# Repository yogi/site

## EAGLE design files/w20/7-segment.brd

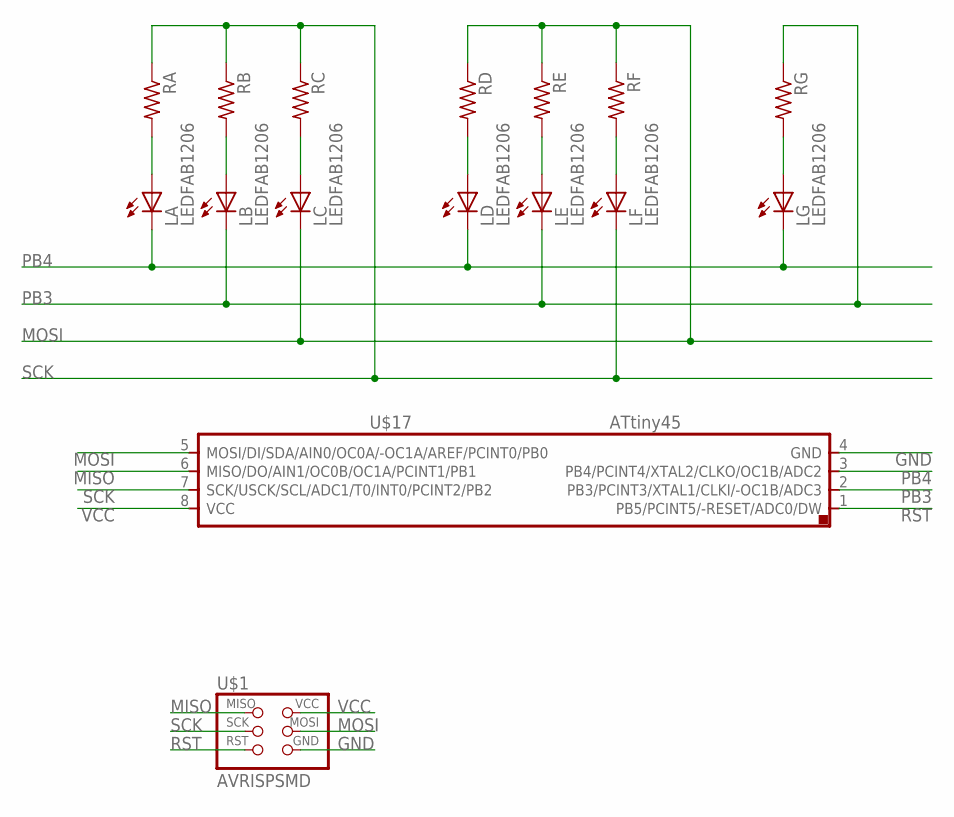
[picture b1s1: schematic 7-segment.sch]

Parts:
LA: LEDFAB1206; LED1206FAB
LB: LEDFAB1206; LED1206FAB
LC: LEDFAB1206; LED1206FAB
LD: LEDFAB1206; LED1206FAB
LE: LEDFAB1206; LED1206FAB
LF: LEDFAB1206; LED1206FAB
LG: LEDFAB1206; LED1206FAB
RA: RES-US1206FAB; R1206FAB
RB: RES-US1206FAB; R1206FAB
RC: RES-US1206FAB; R1206FAB
RD: RES-US1206FAB; R1206FAB
RE: RES-US1206FAB; R1206FAB
RF: RES-US1206FAB; R1206FAB
RG: RES-US1206FAB; R1206FAB
U$1: AVRISPSMD; 2X03SMD
U$17: ATTINY45SI; SOIC8

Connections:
GND: U$1.6 (GND), U$17.4 (GND)
MISO: U$1.1 (MISO), U$17.6 (MISO/DO/AIN1/OC0B/OC1A/PCINT1/PB1)
MOSI: LC.2 (C), RD.1, RE.1, RF.1, U$1.4 (MOSI), U$17.5 (MOSI/DI/SDA/AIN0/OC0A/-OC1A/AREF/PCINT0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)
unnamed: LA.1 (A), RA.2
unnamed: LB.1 (A), RB.2
unnamed: LC.1 (A), RC.2
unnamed: LD.1 (A), RD.2
unnamed: LE.1 (A), RE.2
unnamed: LF.1 (A), RF.2
unnamed: LG.1 (A), RG.2
PB3: LB.2 (C), LE.2 (C), RG.1, U$17.2 (PB3/PCINT3/XTAL1/CLKI/-OC1B/ADC3)
PB4: LA.2 (C), LD.2 (C), LG.2 (C), U$17.3 (PB4/PCINT4/XTAL2/CLKO/OC1B/ADC2)
RST: U$1.5 (RST), U$17.1 (PB5/PCINT5/-RESET/ADC0/DW)
SCK: LF.2 (C), RA.1, RB.1, RC.1, U$1.3 (SCK), U$17.7 (SCK/USCK/SCL/ADC1/T0/INT0/PCINT2/PB2)
VCC: U$1.2 (VCC), U$17.8 (VCC)

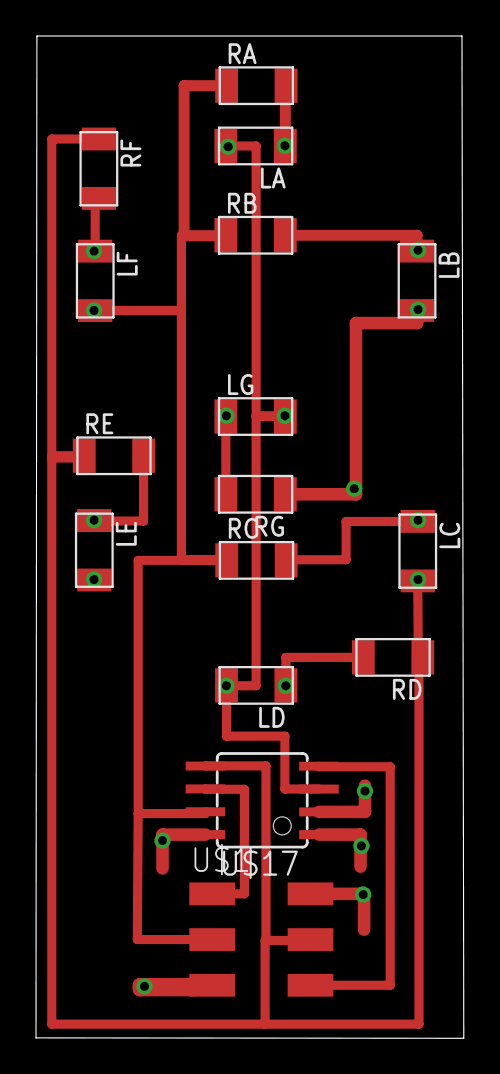
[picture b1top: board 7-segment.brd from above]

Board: 2 copper layers, 23.8 x 55.7 mm, 16 parts (0 on the bottom side), 15 nets.

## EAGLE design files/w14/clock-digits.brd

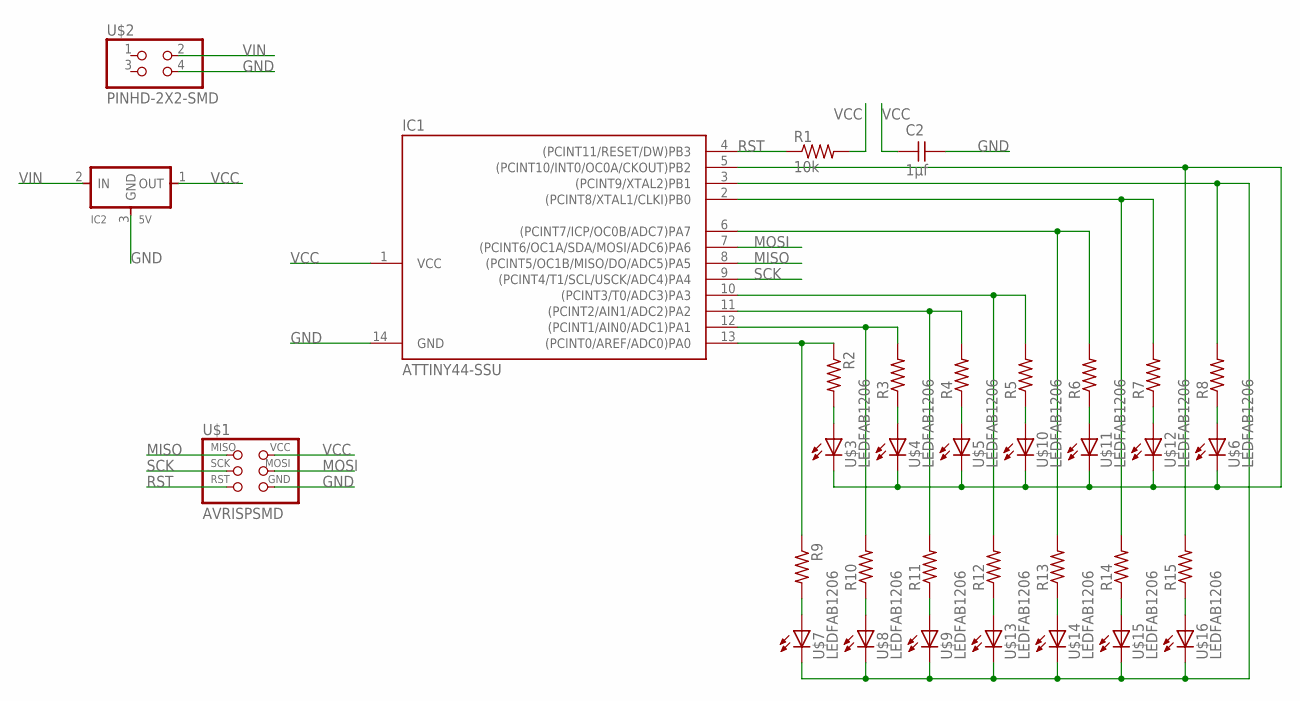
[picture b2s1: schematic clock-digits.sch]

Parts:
C2: 1µf; C1206FAB
IC1: ATTINY44-SSU; SOIC14
IC2: 5V; SOT23
R1: 10k; R1206FAB
R2, R3, R4, R5, R6, R7, R8, R9, R10, R11, R12, R13, R14, R15: RES-US1206FAB; R1206FAB
U$1: AVRISPSMD; 2X03SMD
U$2: PINHD-2X2-SMD; 2X02SMD
U$3, U$4, U$5, U$6, U$7, U$8, U$9, U$10, U$11, U$12, U$13, U$14, U$15, U$16: LEDFAB1206; LED1206FAB

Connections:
GND: C2.2, IC1.14 (GND), IC2.3 (GND), U$1.6 (GND), U$2.4
MISO: IC1.8 ((PCINT5/OC1B/MISO/DO/ADC5)PA5), U$1.1 (MISO)
MOSI: IC1.7 ((PCINT6/OC1A/SDA/MOSI/ADC6)PA6), U$1.4 (MOSI)
unnamed: IC1.13 ((PCINT0/AREF/ADC0)PA0), R2.1, R9.1
unnamed: R2.2, U$3.1 (A)
unnamed: IC1.12 ((PCINT1/AIN0/ADC1)PA1), R3.2, R10.2
unnamed: R3.1, U$4.1 (A)
unnamed: IC1.11 ((PCINT2/AIN1/ADC2)PA2), R4.2, R11.2
unnamed: R4.1, U$5.1 (A)
unnamed: IC1.10 ((PCINT3/T0/ADC3)PA3), R5.2, R12.2
unnamed: R5.1, U$10.1 (A)
unnamed: IC1.6 ((PCINT7/ICP/OC0B/ADC7)PA7), R6.2, R13.2
unnamed: R6.1, U$11.1 (A)
unnamed: IC1.2 ((PCINT8/XTAL1/CLKI)PB0), R7.2, R14.2
unnamed: R7.1, U$12.1 (A)
unnamed: R8.1, U$6.1 (A)
unnamed: IC1.5 ((PCINT10/INT0/OC0A/CKOUT)PB2), R15.2, U$3.2 (C), U$4.2 (C), U$5.2 (C), U$6.2 (C), U$10.2 (C), U$11.2 (C), U$12.2 (C)
unnamed: R9.2, U$7.1 (A)
unnamed: R15.1, U$16.1 (A)
unnamed: R10.1, U$8.1 (A)
unnamed: R11.1, U$9.1 (A)
unnamed: R12.1, U$13.1 (A)
unnamed: R13.1, U$14.1 (A)
unnamed: R14.1, U$15.1 (A)
unnamed: IC1.3 ((PCINT9/XTAL2)PB1), R8.2, U$7.2 (C), U$8.2 (C), U$9.2 (C), U$13.2 (C), U$14.2 (C), U$15.2 (C), U$16.2 (C)
RST: IC1.4 ((PCINT11/RESET/DW)PB3), R1.1, U$1.5 (RST)
SCK: IC1.9 ((PCINT4/T1/SCL/USCK/ADC4)PA4), U$1.3 (SCK)
VCC: C2.1, IC1.1 (VCC), IC2.1 (OUT), R1.2, U$1.2 (VCC)
VIN: IC2.2 (IN), U$2.2

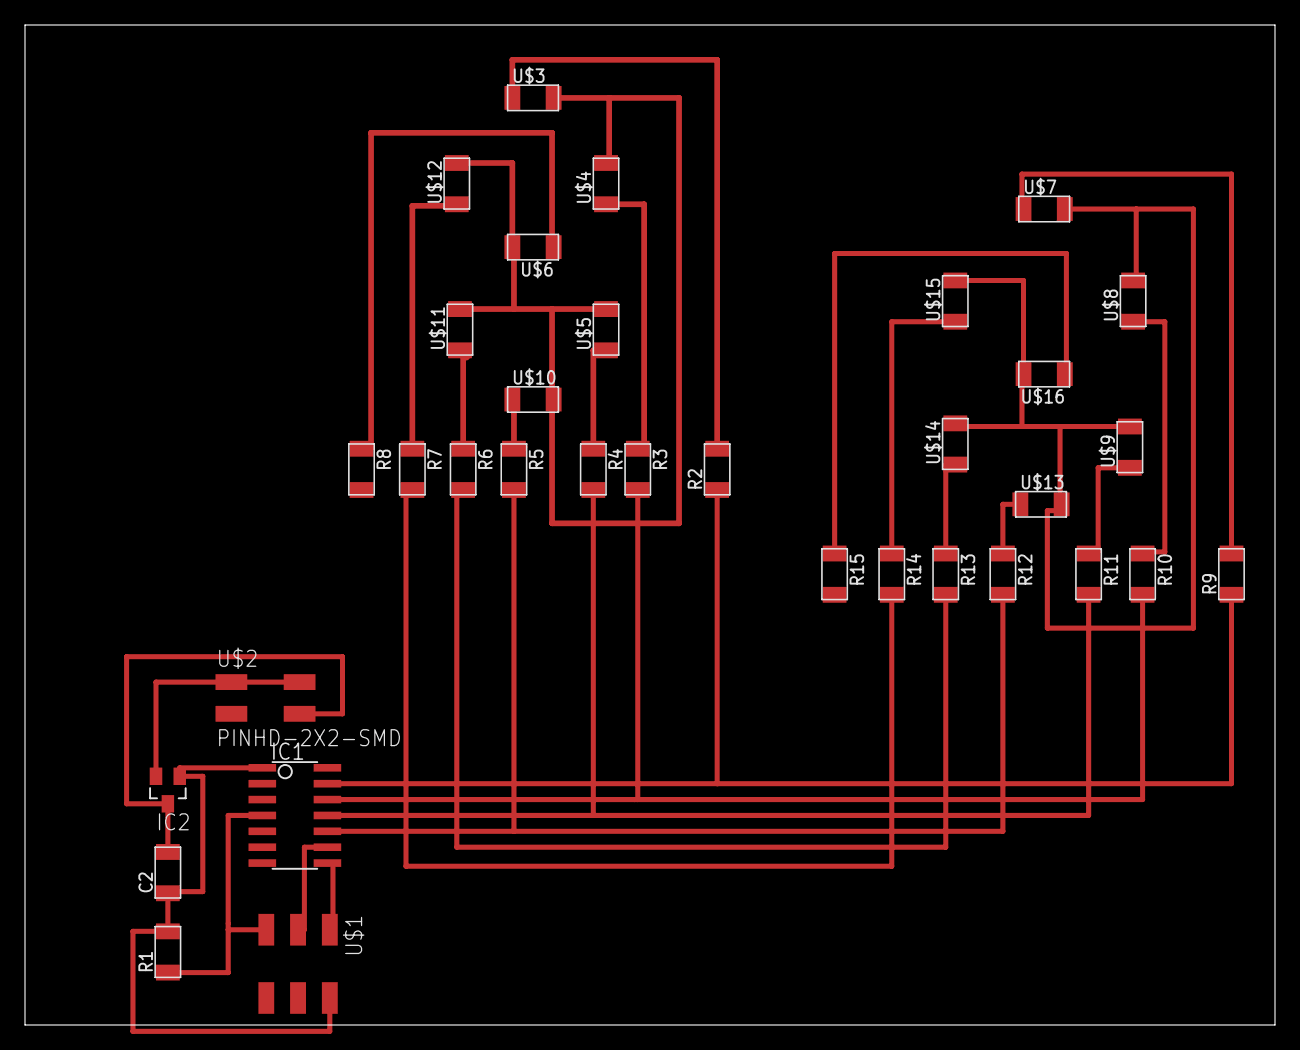
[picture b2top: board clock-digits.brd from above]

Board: 2 copper layers, 100.0 x 80.0 mm, 34 parts (0 on the bottom side), 29 nets.

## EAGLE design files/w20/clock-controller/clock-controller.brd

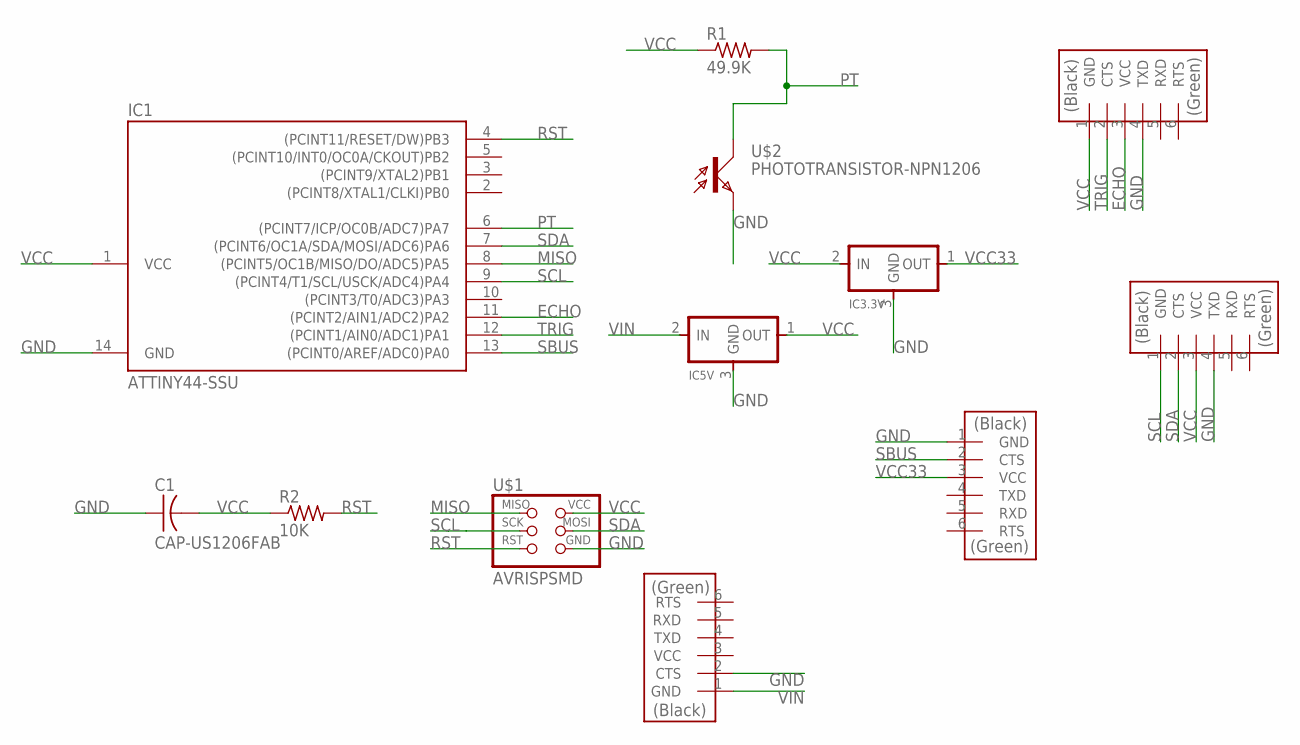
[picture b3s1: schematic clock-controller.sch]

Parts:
C1: CAP-US1206FAB; C1206FAB
DIGITS: FTDI-SMD-HEADER; 1X06SMD
IC1: ATTINY44-SSU; SOIC14
IC3.3V, IC5V: REGULATORSOT23; SOT23
R1: 49.9K; R1206FAB
R2: 10K; R1206FAB
RTC: FTDI-SMD-HEADER; 1X06SMD
U$1: AVRISPSMD; 2X03SMD
U$2: PHOTOTRANSISTOR-NPN1206; OP1206
ULTRA: FTDI-SMD-HEADER; 1X06SMD
USB: FTDI-SMD-HEADER; 1X06SMD

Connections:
ECHO: IC1.11 ((PCINT2/AIN1/ADC2)PA2), ULTRA.3 (VCC)
GND: C1.1, DIGITS.1 (GND), IC1.14 (GND), IC3.3V.3 (GND), IC5V.3 (GND), RTC.4 (TXD), U$1.6 (GND), U$2.EMITTER (E), ULTRA.4 (TXD), USB.2 (CTS)
MISO: IC1.8 ((PCINT5/OC1B/MISO/DO/ADC5)PA5), U$1.1 (MISO)
PT: IC1.6 ((PCINT7/ICP/OC0B/ADC7)PA7), R1.2, U$2.COLLECTOR (C)
RST: IC1.4 ((PCINT11/RESET/DW)PB3), R2.2, U$1.5 (RST)
SBUS: DIGITS.2 (CTS), IC1.13 ((PCINT0/AREF/ADC0)PA0)
SCL: IC1.9 ((PCINT4/T1/SCL/USCK/ADC4)PA4), RTC.1 (GND), U$1.3 (SCK)
SDA: IC1.7 ((PCINT6/OC1A/SDA/MOSI/ADC6)PA6), RTC.2 (CTS), U$1.4 (MOSI)
TRIG: IC1.12 ((PCINT1/AIN0/ADC1)PA1), ULTRA.2 (CTS)
VCC: C1.2, IC1.1 (VCC), IC3.3V.2 (IN), IC5V.1 (OUT), R1.1, R2.1, RTC.3 (VCC), U$1.2 (VCC), ULTRA.1 (GND)
VCC33: DIGITS.3 (VCC), IC3.3V.1 (OUT)
VIN: IC5V.2 (IN), USB.1 (GND)

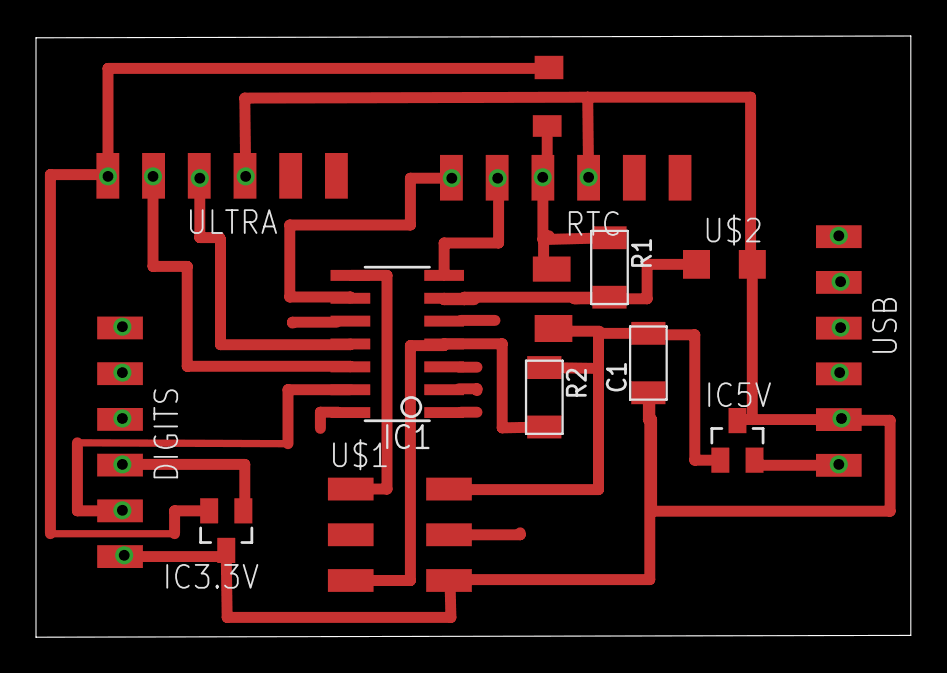
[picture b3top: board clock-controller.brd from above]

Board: 2 copper layers, 48.6 x 33.4 mm, 12 parts (0 on the bottom side), 12 nets.

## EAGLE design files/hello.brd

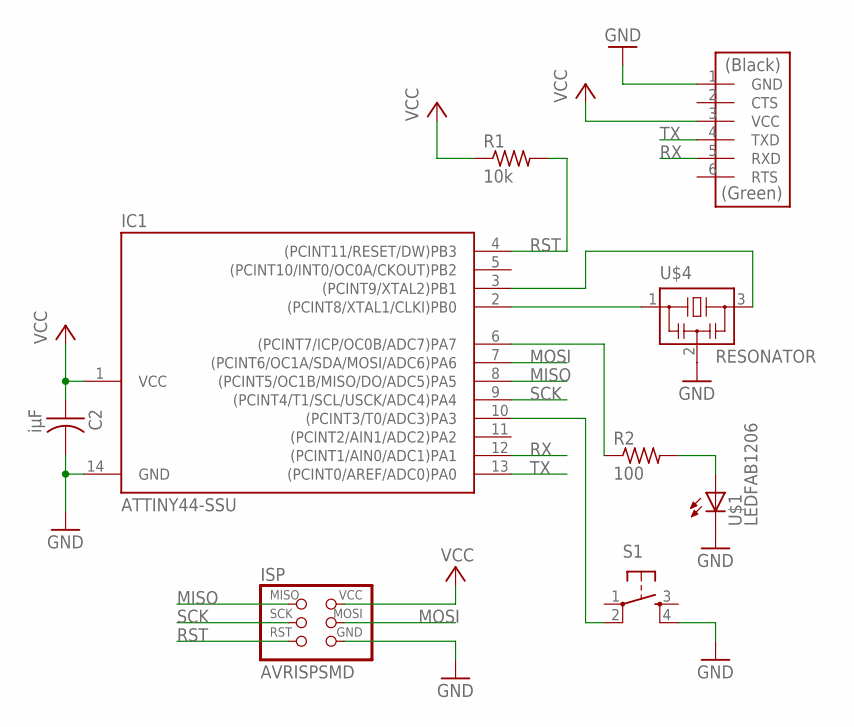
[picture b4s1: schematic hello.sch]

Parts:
C2: iµF; C1206
IC1: ATTINY44-SSU; SOIC14
ISP: AVRISPSMD; 2X03SMD
R1: 10k; R1206
R2: 100; R1206
S1: 6MM_SWITCH6MM_SWITCH; 6MM_SWITCH
U$1: LEDFAB1206; LED1206FAB
U$2: FTDI-SMD-HEADER; 1X06SMD
U$4: RESONATOR; EFOBM

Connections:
GND: C2.2, IC1.14 (GND), ISP.6 (GND), S1.4 (S1), U$1.2 (C), U$2.1 (GND), U$4.2
MISO: IC1.8 ((PCINT5/OC1B/MISO/DO/ADC5)PA5), ISP.1 (MISO)
MOSI: IC1.7 ((PCINT6/OC1A/SDA/MOSI/ADC6)PA6), ISP.4 (MOSI)
unnamed: IC1.2 ((PCINT8/XTAL1/CLKI)PB0), U$4.1
unnamed: IC1.3 ((PCINT9/XTAL2)PB1), U$4.3
unnamed: IC1.6 ((PCINT7/ICP/OC0B/ADC7)PA7), R2.1
unnamed: R2.2, U$1.1 (A)
unnamed: IC1.10 ((PCINT3/T0/ADC3)PA3), S1.2 (P1)
RST: IC1.4 ((PCINT11/RESET/DW)PB3), ISP.5 (RST), R1.2
RX: IC1.12 ((PCINT1/AIN0/ADC1)PA1), U$2.5 (RXD)
SCK: IC1.9 ((PCINT4/T1/SCL/USCK/ADC4)PA4), ISP.3 (SCK)
TX: IC1.13 ((PCINT0/AREF/ADC0)PA0), U$2.4 (TXD)
VCC: C2.1, IC1.1 (VCC), ISP.2 (VCC), R1.1, U$2.3 (VCC)

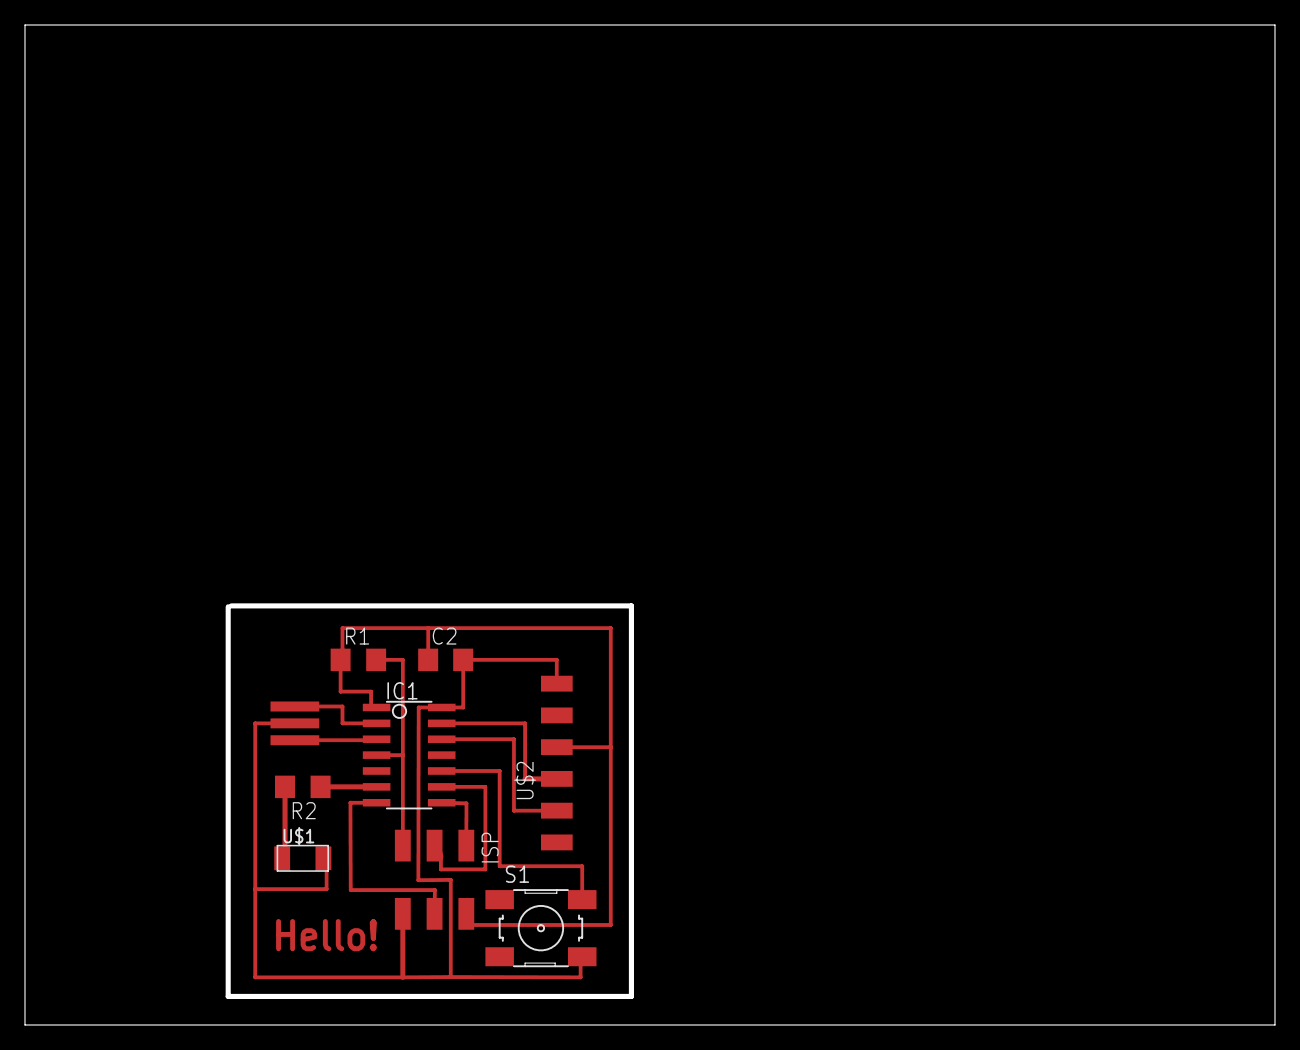
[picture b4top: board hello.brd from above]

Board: 2 copper layers, 100.0 x 80.0 mm, 9 parts (0 on the bottom side), 13 nets.

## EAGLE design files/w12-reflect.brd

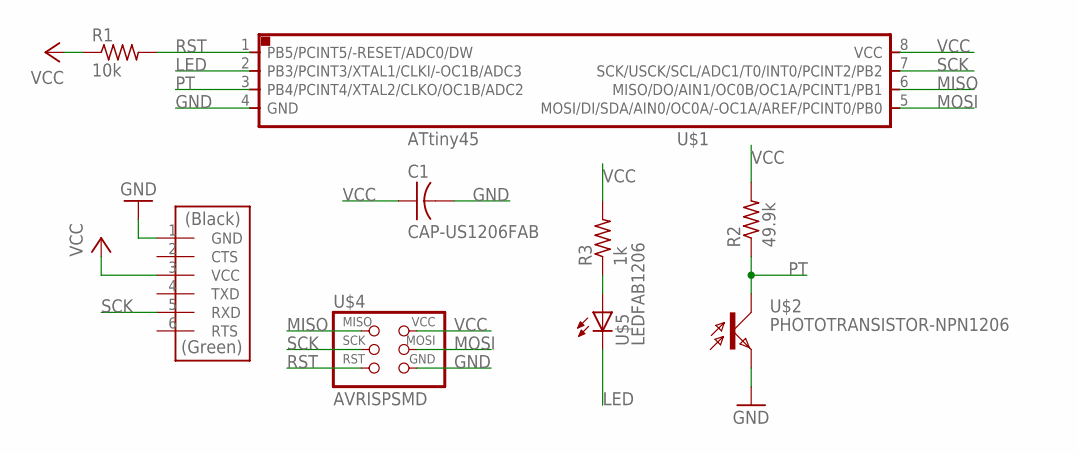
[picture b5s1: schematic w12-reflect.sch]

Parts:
C1: CAP-US1206FAB; C1206FAB
R1: 10k; R1206FAB
R2: 49.9k; R1206FAB
R3: 1k; R1206FAB
U$1: ATTINY45SI; SOIC8
U$2: PHOTOTRANSISTOR-NPN1206; OP1206
U$3: FTDI-SMD-HEADER; 1X06SMD
U$4: AVRISPSMD; 2X03SMD
U$5: LEDFAB1206; LED1206FAB

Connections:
GND: C1.2, U$1.4 (GND), U$2.EMITTER (E), U$3.1 (GND), U$4.6 (GND)
LED: U$1.2 (PB3/PCINT3/XTAL1/CLKI/-OC1B/ADC3), U$5.2 (C)
MISO: U$1.6 (MISO/DO/AIN1/OC0B/OC1A/PCINT1/PB1), U$4.1 (MISO)
MOSI: U$1.5 (MOSI/DI/SDA/AIN0/OC0A/-OC1A/AREF/PCINT0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), U$4.4 (MOSI)
unnamed: R3.1, U$5.1 (A)
PT: R2.1, U$1.3 (PB4/PCINT4/XTAL2/CLKO/OC1B/ADC2), U$2.COLLECTOR (C)
RST: R1.2, U$1.1 (PB5/PCINT5/-RESET/ADC0/DW), U$4.5 (RST)
SCK: U$1.7 (SCK/USCK/SCL/ADC1/T0/INT0/PCINT2/PB2), U$3.5 (RXD), U$4.3 (SCK)
VCC: C1.1, R1.1, R2.2, R3.2, U$1.8 (VCC), U$3.3 (VCC), U$4.2 (VCC)

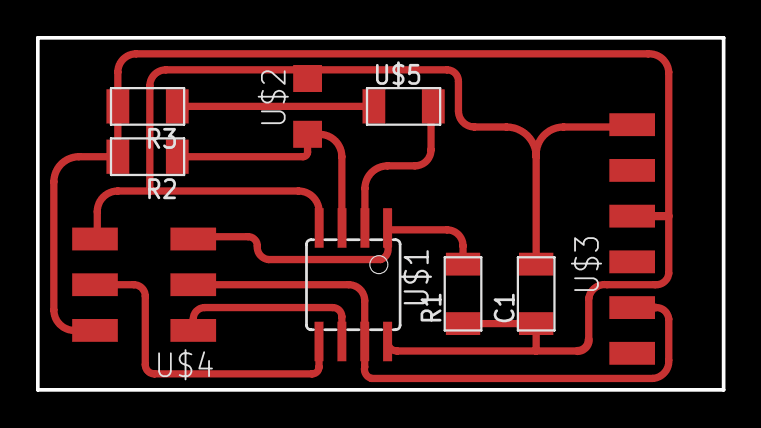
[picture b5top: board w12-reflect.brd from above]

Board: 2 copper layers, 38.1 x 19.6 mm, 9 parts (0 on the bottom side), 9 nets.

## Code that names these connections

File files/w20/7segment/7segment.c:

#include <avr/io.h>
#include <util/delay.h>
#include "avr/interrupt.h"

#define SCK_PIN PB2
#define MOSI_PIN PB0

#define ABC_ANODE   SCK_PIN
#define A           PB4
#define B           PB3
#define C           MOSI_PIN

#define DEF_ANODE   MOSI_PIN
#define D           PB4
#define E           PB3
#define F           SCK_PIN

#define G_ANODE     PB3
#define G           PB4

#define DIR_REG   DDRB

#define output(pin) (DIR_REG |= (1 << pin)) // set port direction for output
#define input(pin) (DIR_REG &= (~ (1 << pin))) // set port direction for input
#define set(pin) (PORTB |= (1 << pin)) // set port pin
#define clear(pin) (PORTB &= (~ (1 << pin))) // clear port pin

const int FLASH_DELAY_MS = 1;
const int DIGIT_DISPLAY_MS = 1000;

char DIGIT_SEGMENTS[10][7] = {
     {'A', 'B', 'C', 'D', 'E', 'F'},            // 0
     {'B', 'C'},                                // 1
     {'A', 'B', 'D', 'E', 'G'},                 // 2
     {'A', 'B', 'C', 'D', 'G'},                 // 3
     {'B', 'C', 'F', 'G'},                      // 4
     {'A', 'C', 'D', 'F', 'G'},                 // 5
     {'A', 'C', 'D', 'E', 'F', 'G'},            // 6
     {'A', 'B', 'C'},                           // 7
     {'A', 'B', 'C', 'D', 'E', 'F', 'G',},      // 8
     {'A', 'B', 'C', 'F', 'G',}                 // 9
};

int DIGIT_NUM_SEGMENTS[] = {
    6, // 0
    2, // 1
    5, // 2
    5, // 3
    4, // 4
    5, // 5
    6, // 6
    3, // 7
    7, // 8
    5  // 9
};



#define pin_test(pins,pin) (pins & pin) // test for port pin
#define bit_test(byte,bit) (byte & (1 << bit)) // test for bit set
#define bit_delay_time 100 // bit delay for 9600 with overhead
#define bit_delay() _delay_us(bit_delay_time) // RS232 bit delay
#define half_bit_delay() _delay_us(bit_delay_time/2) // RS232 half bit delay
#define led_delay() _delay_ms(100) // LED flash delay

#define START_BIT_CHECK_TIMEOUT 2 // 5 ms

#define serial_pins PINB
#define SERIAL_IN_PIN (1 << PB1)

volatile char digit = 1;


int anode_pin_for(char led) {
    if (led == 'A' || led == 'B' || led == 'C') 
        return ABC_ANODE;
    else if (led == 'D' || led == 'E' || led == 'F') 
        return DEF_ANODE;
    else  
        return G_ANODE;
}

int led_pin_for(char led) {
    if (led == 'A' || led == 'D' || led == 'G')
        return PB4;
    else if (led == 'B' || led == 'E')
        return PB3;
    else if (led == 'C')
        return MOSI_PIN;
    else // 'F'
        return SCK_PIN;
}

void high_impedance(pin) {
    input(pin);
    clear(pin);
}

void flash(char led) {
    int anode_pin = anode_pin_for(led);
    int led_pin = led_pin_for(led);
    
    output(anode_pin);    
    output(led_pin);
        
    set(anode_pin);
    clear(led_pin);

    _delay_ms(FLASH_DELAY_MS);
    
    high_impedance(anode_pin);    
    high_impedance(led_pin);
}

void flash_segments(char segments[], int len) {
    int i;
    for (i = 0; i < len; i++) {
        flash(segments[i]);
    }
}

void display(int digit, int duration_ms) {
    int i;
    char *segments = DIGIT_SEGMENTS[digit];
    int num_segments = DIGIT_NUM_SEGMENTS[digit];
    int cycles = duration_ms / (FLASH_DELAY_MS * num_segments);
    for (i = 0; i < cycles; i++) {
        flash_segments(segments, num_segments);
    }
}

int main(void) {
    int i = 0;
    while(1) {
        display(i, DIGIT_DISPLAY_MS);
        _delay_ms(1000);
        if (++i >= 10)
            i = 0;
    }
    
    return 0;
}

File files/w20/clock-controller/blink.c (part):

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
#define digit_bus_port PORTA
#define digit_bus_direction DDRA
#define digit_bus_pin_out (1 << PA0)

#define serial_port PORTB
#define serial_direction DDRB
#define serial_pin_out (1 << PB2)

#define trigger_port PORTA
#define trigger_direction DDRA
#define trigger_pin_out (1 << PA1)

#define echo_port PORTA
#define echo_direction DDRA
#define echo_pin_in (1 << PA2)
#define echo_pins PINA

#define TURN_OFF_DISPLAY 11
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
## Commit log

2022-05-10 init
2022-05-12 update build dir
